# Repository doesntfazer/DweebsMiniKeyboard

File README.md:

# DweebsMiniKeyboard

This is the Dweebs Mini Keyboard By Keyboard Dweebs. Since Keyboard Dweebs is out of business I have decided to open source the hardware. Feel free to do whatever you want. This is licenced under the GPL

Firmware is not in the main QMK commit, 
You can find it here https://github.com/doesntfazer/qmk_firmware/tree/dweebs/keyboards/dweebsmini

It is virtually identical to a let's split when it comes to the wiring. So if you find a guide for that, it will be basically the same thing.

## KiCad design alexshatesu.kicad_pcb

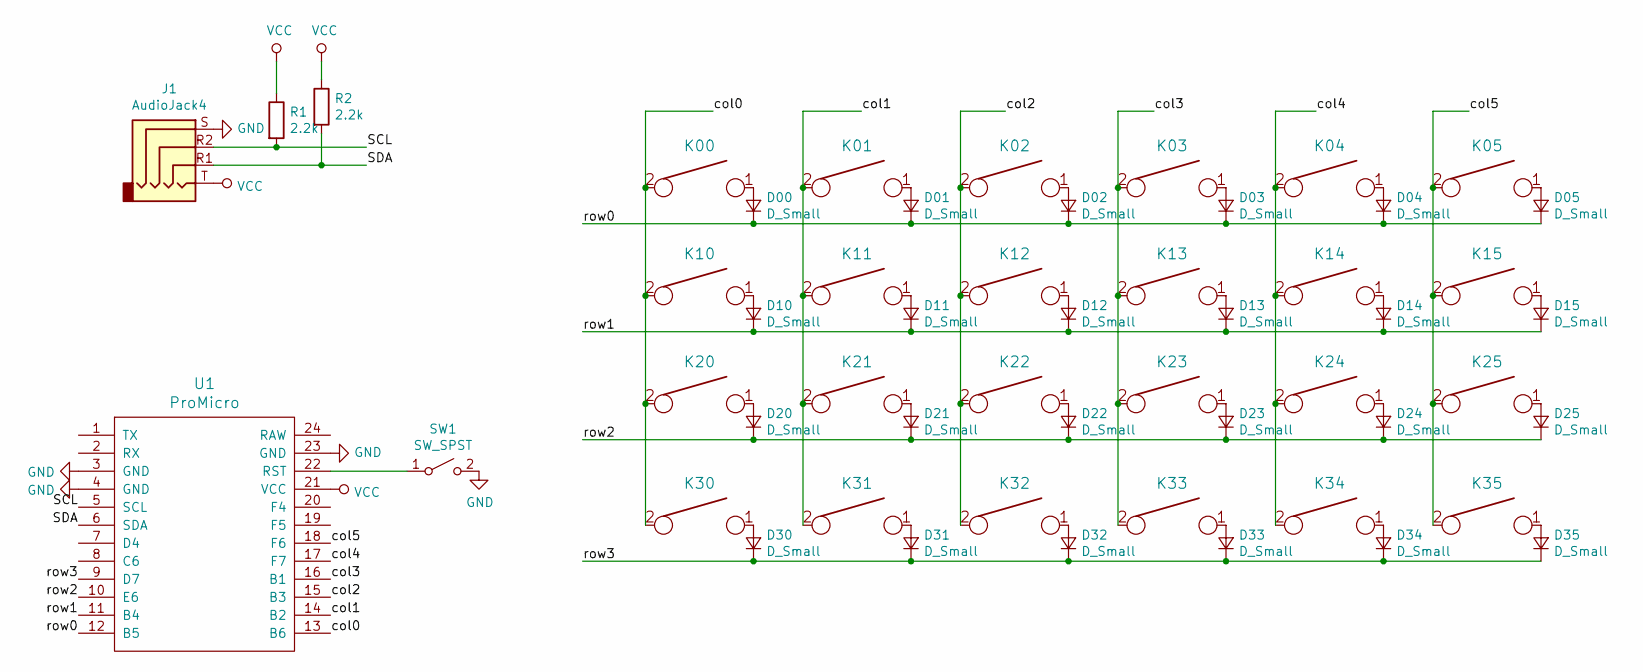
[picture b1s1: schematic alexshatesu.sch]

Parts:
D00, D01, D02, D03, D04, D05, D10, D11, D12, D13, D14, D15, D20, D21, D22, D23, D24, D25, D30, D31, D32, D33, D34, D35: D_Small; D_SOD123_axial_doublesided
J1: AudioJack4; MJ-4PP-9
K00, K01, K02, K03, K04, K05, K10, K11, K12, K13, K14, K15, K20, K21, K22, K23, K24, K25, K30, K31, K32, K33, K34, K35: KEYSW; Mx_Alps_100-dualside
R1, R2: 2.2k; R_0805_TH_DualSided
SW1: SW_SPST; SW_Tactile_SPST_Angled_PTS645Vx39-2LFS
U1: ProMicro; Pro_Micro

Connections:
/SCL: J1.R2, R1.2, U1.5 (SCL)
/SDA: J1.R1, R2.2, U1.6 (SDA)
/col0: K00.2, K10.2, K20.2, K30.2, U1.13 (B6)
/col1: K01.2, K11.2, K21.2, K31.2, U1.14 (B2)
/col2: K02.2, K12.2, K22.2, K32.2, U1.15 (B3)
/col3: K03.2, K13.2, K23.2, K33.2, U1.16 (B1)
/col4: K04.2, K14.2, K24.2, K34.2, U1.17 (F7)
/col5: K05.2, K15.2, K25.2, K35.2, U1.18 (F6)
/row0: D00.1 (K), D01.1 (K), D02.1 (K), D03.1 (K), D04.1 (K), D05.1 (K), U1.12 (B5)
/row1: D10.1 (K), D11.1 (K), D12.1 (K), D13.1 (K), D14.1 (K), D15.1 (K), U1.11 (B4)
/row2: D20.1 (K), D21.1 (K), D22.1 (K), D23.1 (K), D24.1 (K), D25.1 (K), U1.10 (E6)
/row3: D30.1 (K), D31.1 (K), D32.1 (K), D33.1 (K), D34.1 (K), D35.1 (K), U1.9 (D7)
GND: J1.S, SW1.2 (B), U1.3 (GND), U1.4 (GND), U1.23 (GND)
unnamed: D00.2 (A), K00.1
unnamed: D01.2 (A), K01.1
unnamed: D02.2 (A), K02.1
unnamed: D03.2 (A), K03.1
unnamed: D04.2 (A), K04.1
unnamed: D05.2 (A), K05.1
unnamed: D10.2 (A), K10.1
unnamed: D11.2 (A), K11.1
unnamed: D12.2 (A), K12.1
unnamed: D13.2 (A), K13.1
unnamed: D14.2 (A), K14.1
unnamed: D15.2 (A), K15.1
unnamed: D20.2 (A), K20.1
unnamed: D21.2 (A), K21.1
unnamed: D22.2 (A), K22.1
unnamed: D23.2 (A), K23.1
unnamed: D24.2 (A), K24.1
unnamed: D25.2 (A), K25.1
unnamed: D30.2 (A), K30.1
unnamed: D31.2 (A), K31.1
unnamed: D32.2 (A), K32.1
unnamed: D33.2 (A), K33.1
unnamed: D34.2 (A), K34.1
unnamed: D35.2 (A), K35.1
unnamed: SW1.1 (A), U1.22 (RST)
VCC: J1.T, R1.1, R2.1, U1.21 (VCC)

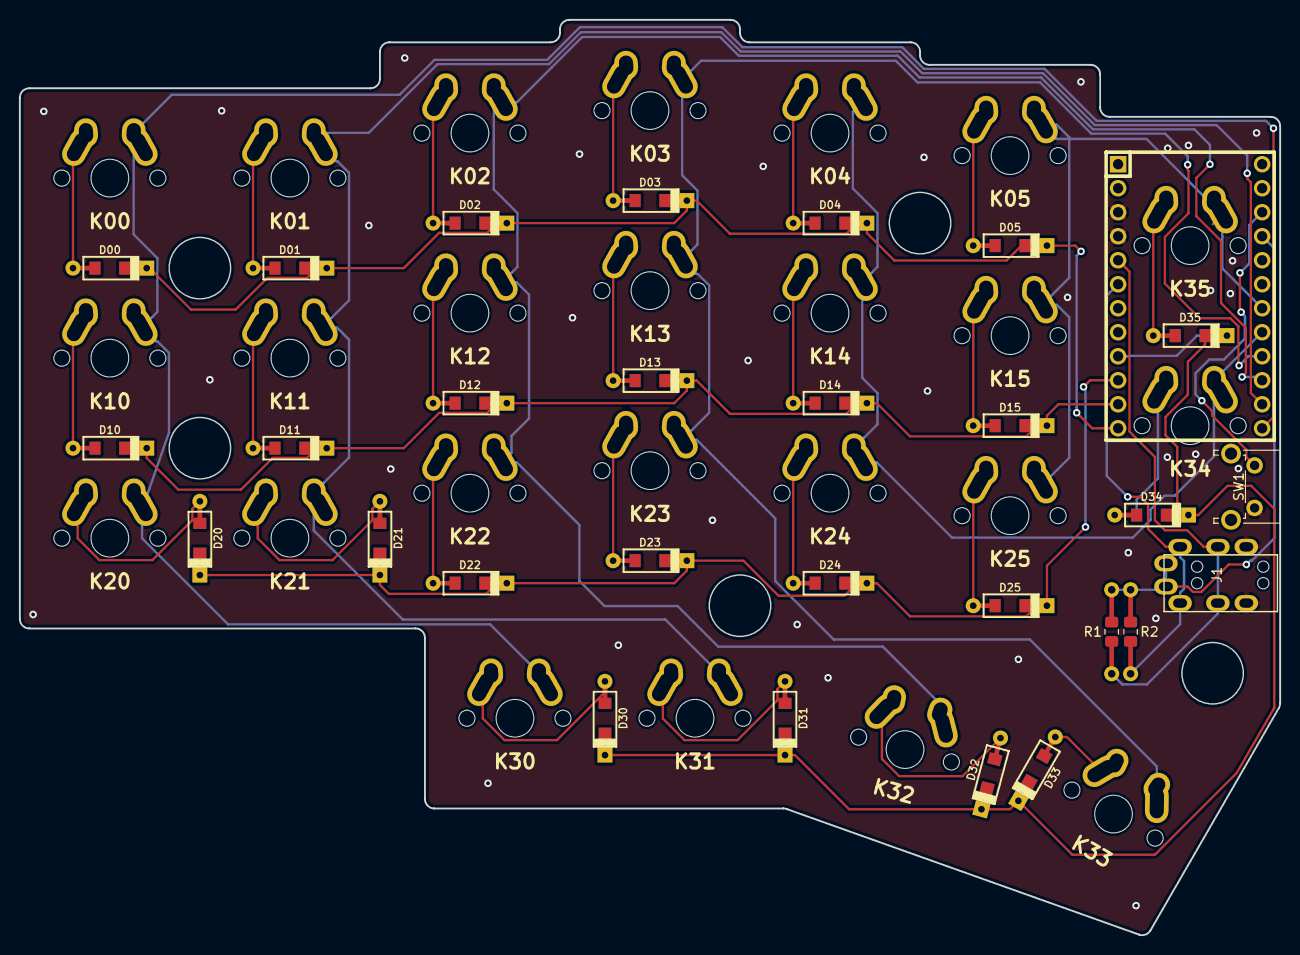
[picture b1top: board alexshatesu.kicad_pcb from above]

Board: 2 copper layers, 133.3 x 96.8 mm, 53 parts (0 on the bottom side), 39 nets.
